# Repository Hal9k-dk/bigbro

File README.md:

# BigBro

BigBro is the system used by Hal9K to control access to its different advanced
machines, with RFID based access control.

The system is designed to cut power to the machines if no valid key-card is present
or in the special case of a 3D printer, if no special key-card is present, 
and a print isn't ongoing.

The first version of BigBro was designed around the ESP8266, specifically the WEMOS D1 mini.
Version 2 uses ESP32 with the [EspressIf ESP-IDF](https://idf.espressif.com/).

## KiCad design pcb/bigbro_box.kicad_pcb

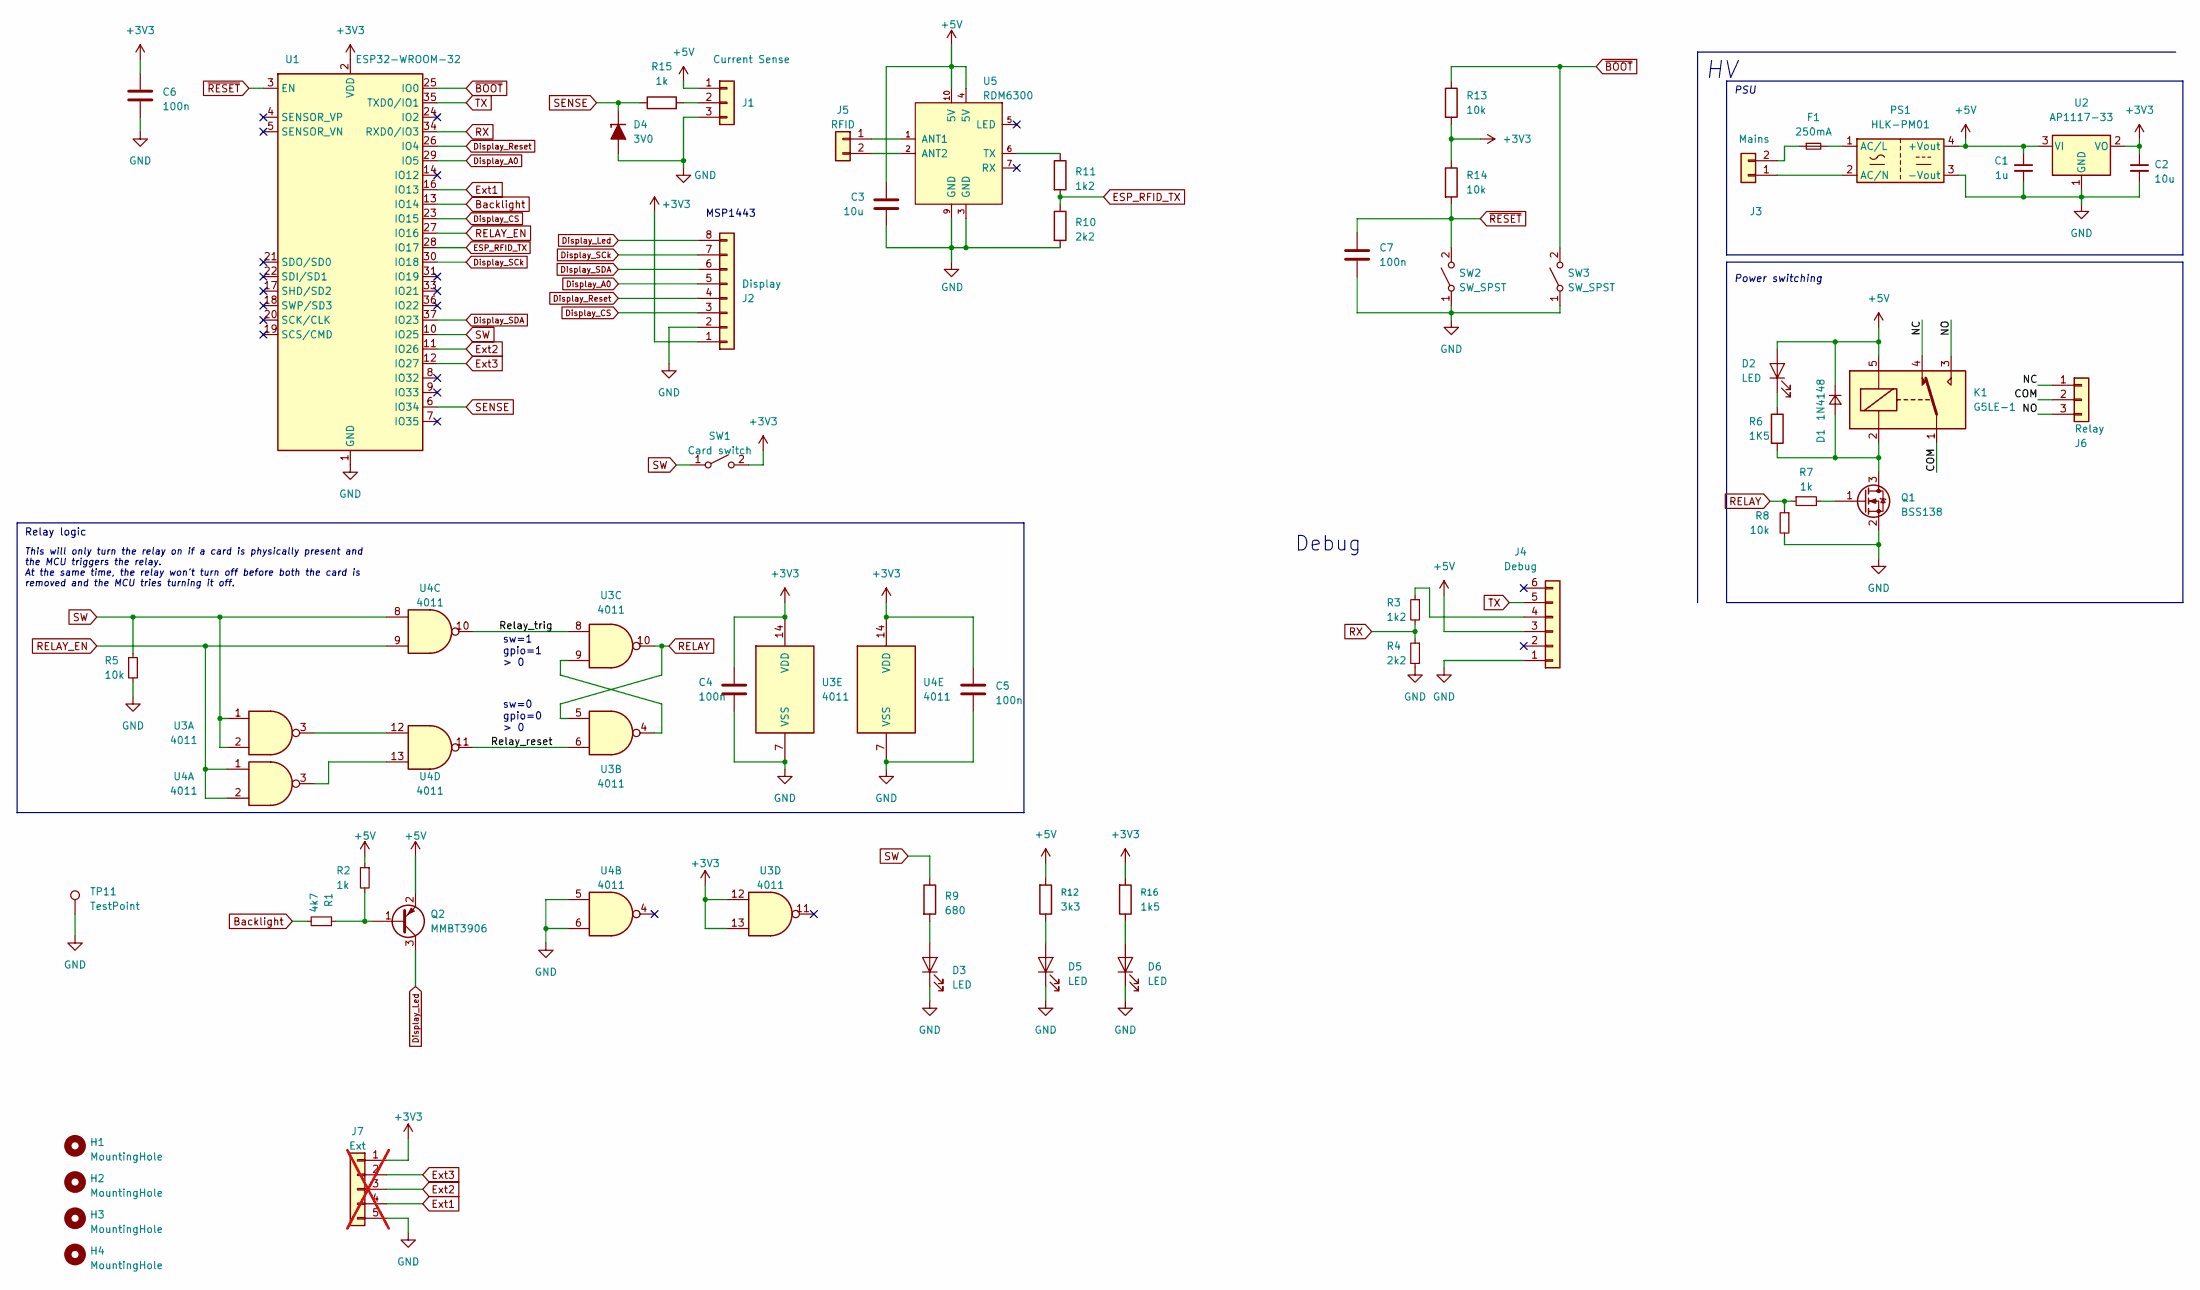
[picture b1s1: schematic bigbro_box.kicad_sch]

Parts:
C1: 1u; C_0603_1608Metric; LCSC C15849
C2: 10u; C_0603_1608Metric; LCSC C96446
C3: 10u; C_0603_1608Metric
C4, C5, C6: 100n; C_0603_1608Metric; LCSC C14663
C7: 100n; C_0603_1608Metric
D1: 1N4148; D_SOD-123
D2, D3, D5, D6: LED; LED_0603_1608Metric
D4: 3V0; D_MiniMELF
F1: 250mA; Fuse_Littelfuse_395Series
H1, H2, H3, H4: MountingHole; MountingHole_3.2mm_M3
J1: Current Sense; JST_XH_B3B-XH-A_1x03_P2.50mm_Vertical; LCSC C144394
J2: Display; PinSocket_1x08_P2.54mm_Vertical
J3: Mains; PhoenixContact_MSTBVA_2,5_2-G-5,08_1x02_P5.08mm_Vertical
J4: Debug; PinHeader_1x06_P2.54mm_Vertical; LCSC C37208
J5: RFID; JST_XH_B2B-XH-A_1x02_P2.50mm_Vertical
J6: Relay; PhoenixContact_MSTBVA_2,5_3-G-5,08_1x03_P5.08mm_Vertical
J7: Ext; PinHeader_1x05_P2.54mm_Vertical; not fitted
K1: G5LE-1; Relay_SPDT_Omron-G5LE-1
PS1: HLK-PM01; Converter_ACDC_HiLink_HLK-PMxx
Q1: BSS138; SOT-23
Q2: MMBT3906; SOT-23
R1: 4k7; R_0603_1608Metric; LCSC C23162
R2, R7: 1k; R_0603_1608Metric; LCSC C14676
R3: 1k2; R_0603_1608Metric; LCSC C22765
R4: 2k2; R_0603_1608Metric; LCSC C5362360
R5, R8: 10k; R_0603_1608Metric; LCSC C15401
R6: 1K5; R_0603_1608Metric; LCSC C22843
R9: 680; R_0603_1608Metric
R10: 2k2; R_0603_1608Metric
R11: 1k2; R_0603_1608Metric
R12: 3k3; R_0603_1608Metric
R13, R14: 10k; R_0603_1608Metric
R15: 1k; R_0603_1608Metric
R16: 1k5; R_0603_1608Metric
SW1: Card switch; JST_XH_B2B-XH-A_1x02_P2.50mm_Vertical
SW2, SW3: SW_SPST; SW_SPST_CK_RS282G05A3
TP11: TestPoint; TestPoint_Keystone_5000-5004_Miniature
U1: ESP32-WROOM-32; LCSC C95209
U2: AP1117-33; SOT-223-3_TabPin2
U3, U4: 4011; SOIC-14_3.9x8.7mm_P1.27mm
U5: RDM6300; RDM6300_B38.5x18.2mm

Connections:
+3V3: C2.1, C4.1, C5.1, C6.1, J2.1, J7.1, R13.2, R14.1, R16.1, SW1.2 (B), U1.2 (VDD), U2.2 (VO), U3.12, U3.13, U3.14 (VDD), U4.14 (VDD)
+5V: C1.1, C3.1, D1.1 (K), D2.2 (A), J1.1, J4.3, K1.5, PS1.4 (+Vout), Q2.2 (E), R2.1, R12.1, U2.3 (VI), U5.4 (5V), U5.10 (5V)
/COM: J6.2, K1.1
/NC: J6.1, K1.4
/NO: J6.3, K1.3
/Relay_reset: U3.6, U4.11
/Relay_trig: U3.8, U4.10
Backlight: R1.2, U1.13 (IO14)
Display_A0: J2.5, U1.29 (IO5)
Display_CS: J2.3, U1.23 (IO15)
Display_Led: J2.8, Q2.3 (C)
Display_Reset: J2.4, U1.26 (IO4)
Display_SCk: J2.7, U1.30 (IO18)
Display_SDA: J2.6, U1.37 (IO23)
ESP_RFID_TX: R10.1, R11.2, U1.28 (IO17)
Ext1: J7.4, U1.16 (IO13)
Ext2: J7.3, U1.11 (IO26)
Ext3: J7.2, U1.12 (IO27)
GND: C1.2, C2.2, C3.2, C4.2, C5.2, C6.2, C7.2, D3.1 (K), D4.2 (A), D5.1 (K), D6.1 (K), J1.3, J2.2, J4.1, J7.5, PS1.3 (-Vout), Q1.2 (S), R4.2, R5.2, R8.2, R10.2, SW2.1 (A), SW3.1 (A), TP11.1 (1_1), U1.1 (GND), U1.15 (GND), U1.38 (GND), U1.39 (GND), U2.1 (GND), U3.7 (VSS), U4.5, U4.6, U4.7 (VSS), U5.3 (GND), U5.9 (GND)
unnamed: D1.2 (A), K1.2, Q1.3 (D), R6.2
unnamed: D2.1 (K), R6.1
unnamed: D3.2 (A), R9.2
unnamed: D5.2 (A), R12.2
unnamed: D6.2 (A), R16.2
unnamed: J1.2, R15.2
unnamed: J3.1, PS1.2 (AC/N)
unnamed: F1.1, J3.2
unnamed: J4.4, R3.1
unnamed: J5.1, U5.1 (ANT1)
unnamed: J5.2, U5.2 (ANT2)
unnamed: F1.2, PS1.1 (AC/L)
unnamed: Q1.1 (G), R7.2
unnamed: Q2.1 (B), R1.1, R2.2
unnamed: U3.3, U4.12
unnamed: U3.4, U3.9
unnamed: U4.3, U4.13
unnamed: R11.1, U5.6 (TX)
RELAY: R7.1, R8.1, U3.5, U3.10
RELAY_EN: U1.27 (IO16), U4.1, U4.2, U4.9
RX: R3.2, R4.1, U1.34 (RXD0/IO3)
SENSE: D4.1 (K), R15.1, U1.6 (IO34)
SW: R5.1, R9.1, SW1.1 (A), U1.10 (IO25), U3.1, U3.2, U4.8
TX: J4.5, U1.35 (TXD0/IO1)
~BOOT: R13.1, SW3.2 (B), U1.25 (IO0)
~RESET: C7.1, R14.2, SW2.2 (B), U1.3 (EN)

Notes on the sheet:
Power switching
Relay logic
sw=1 gpio=1 > 0
This will only turn the relay on if a card is physically present and the MCU triggers the relay. At the same time, the relay won't turn off before both the card is removed and the MCU tries turning it off.
Debug
sw=0 gpio=0 > 0
MSP1443
PSU

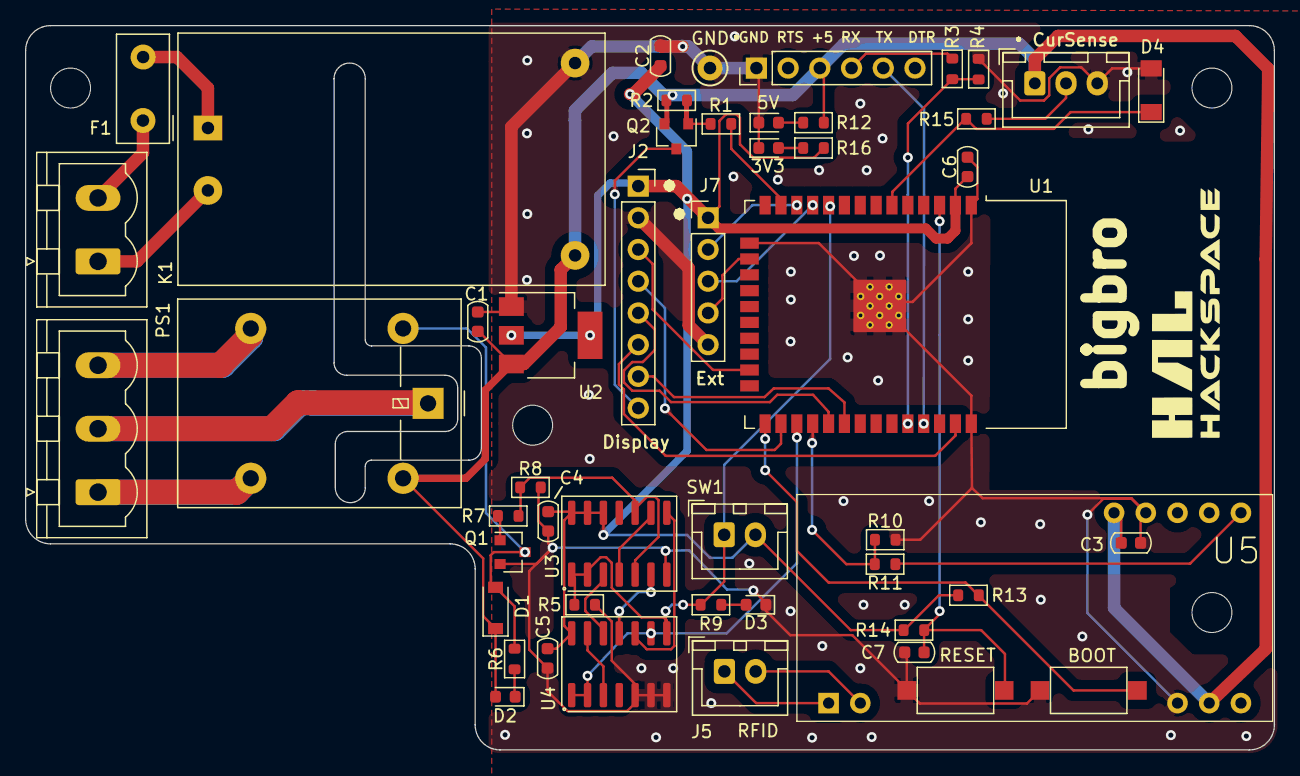
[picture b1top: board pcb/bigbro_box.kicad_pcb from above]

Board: 2 copper layers, 100.0 x 58.0 mm, 54 parts (0 on the bottom side), 45 nets.

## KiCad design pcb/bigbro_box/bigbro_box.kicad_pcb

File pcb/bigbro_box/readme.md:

# Bigbro Box

This is V2 of the access control boxes used on the machines in Hal9k.

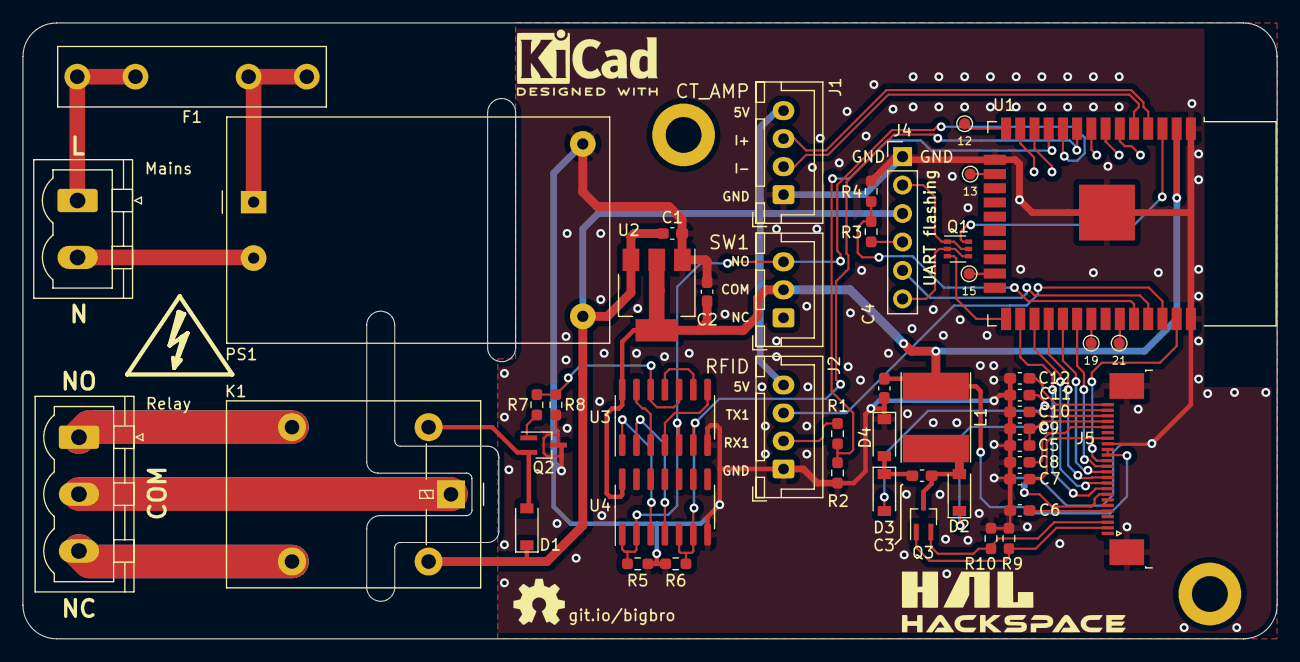
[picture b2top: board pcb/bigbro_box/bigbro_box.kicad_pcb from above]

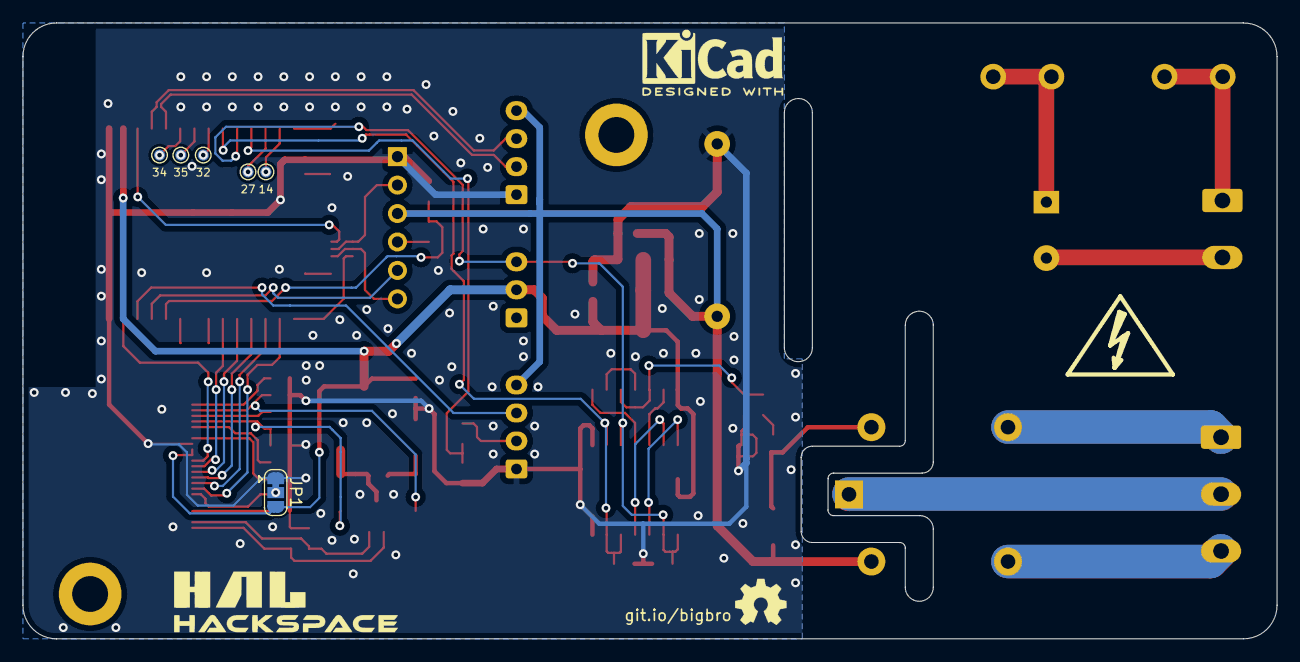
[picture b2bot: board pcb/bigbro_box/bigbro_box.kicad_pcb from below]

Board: 2 copper layers, 112.0 x 55.0 mm, 55 parts (6 on the bottom side), 59 nets.

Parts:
C1, C6, C7, C8, C9, C10, C11, C12: 1uF; C_0603_1608Metric_Pad1.08x0.95mm_HandSolder
C2: 10uF; C_0603_1608Metric_Pad1.08x0.95mm_HandSolder
C3, C4, C5: 4.7uF; C_0603_1608Metric_Pad1.08x0.95mm_HandSolder
D1: D_Small; D_SOD-123
D2, D3, D4: MBR0530; D_SOD-123
F1: 250mA; Fuseholder_Littelfuse_445_030_series_5x20mm
J1: CT_AMP; JST_XH_B4B-XH-A_1x04_P2.50mm_Vertical
J2: RFID; JST_XH_B4B-XH-A_1x04_P2.50mm_Vertical
J3: Mains; PhoenixContact_MSTBVA_2,5_2-G-5,08_1x02_P5.08mm_Vertical
J4: UART flashing; PinHeader_1x06_P2.54mm_Vertical
J5: 2-1734839-4; TE_2-1734839-4_1x24-1MP_P0.5mm_Horizontal
J6: Relay; PhoenixContact_MSTBVA_2,5_3-G-5,08_1x03_P5.08mm_Vertical
JP1: D_BS; SolderJumper-3_P1.3mm_Bridged12_RoundedPad1.0x1.5mm
K1: G5LE-1; Relay_SPDT_Omron-G5LE-1
L1: 47uH; L_Taiyo-Yuden_NR-60xx_HandSoldering
PS1: HLK-PM01; Converter_ACDC_HiLink_HLK-PMxx
Q1: ADC114YUQ; SOT-363_SC-70-6
Q2: Q_NMOS_GDS; SOT-323_SC-70_Handsoldering
Q3: Si1308EDL; SOT-323_SC-70_Handsoldering
R1, R3: 1k2; R_0603_1608Metric_Pad0.98x0.95mm_HandSolder
R2, R4: 2k2; R_0603_1608Metric_Pad0.98x0.95mm_HandSolder
R5, R6, R8: 10k; R_0603_1608Metric_Pad0.98x0.95mm_HandSolder
R7: 1k; R_0603_1608Metric_Pad0.98x0.95mm_HandSolder
R9: 1M; R_0603_1608Metric_Pad0.98x0.95mm_HandSolder
R10: 2R2; R_0603_1608Metric_Pad0.98x0.95mm_HandSolder
SW1: SW_SPDT; JST_XH_B3B-XH-A_1x03_P2.50mm_Vertical
TP1: 12; TestPoint_Pad_D1.0mm
TP2: 13; TestPoint_Pad_D1.0mm
TP3: 14; TestPoint_Pad_D1.0mm
TP4: 15; TestPoint_Pad_D1.0mm
TP5: 19; TestPoint_Pad_D1.0mm
TP6: 21; TestPoint_Pad_D1.0mm
TP7: 27; TestPoint_Pad_D1.0mm
TP8: 32; TestPoint_Pad_D1.0mm
TP9: 34; TestPoint_Pad_D1.0mm
TP10: 35; TestPoint_Pad_D1.0mm
U1: ESP32-WROOM-32
U2: AP1117-33; SOT-223-3_TabPin2
U3, U4: 4011; SOIC-14_3.9x8.7mm_P1.27mm

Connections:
+3V3: C2.1, C4.2, J5.15, J5.16, JP1.3 (B), L1.1, SW1.2 (B), U1.2 (VDD), U2.2 (VO), U3.14 (VDD), U4.14 (VDD)
+5V: C1.1, D1.1 (K), J1.4, J2.4, J4.3, K1.5, PS1.4 (+Vout), U2.3 (VI)
/COM: J6.2, K1.1
/D_BUSY: J5.9, U1.26 (IO4)
/Display/BS1: J5.8, JP1.2 (C)
/Display/GDR: J5.2, Q3.1 (G), R9.1
/Display/RESE: J5.3, Q3.2 (S), R10.1
/Display/VCOM: C12.2, J5.24
/Display/VDD: C7.2, J5.18
/Display/VGH: C5.2, C9.2, D2.1 (K), J5.21
/Display/VGL: C11.2, D3.2 (A), J5.23
/Display/VSH1: C8.2, J5.20
/Display/VSH2: C6.2, J5.5
/Display/VSL: C10.2, J5.22
/I_Sens+: J1.3, U1.4 (SENSOR_VP)
/I_Sens-: J1.2, U1.5 (SENSOR_VN)
/L_in: F1.1, J3.1
/MCU_RX0: R3.2, R4.1, U1.34 (RXD0/IO3)
/MCU_RX1: R1.2, R2.1, U1.11 (IO26)
/MCU_TX0: J4.5, U1.35 (TXD0/IO1)
/MCU_TX1: J2.3, U1.36 (IO22)
/NC: J6.3, K1.4
/NO: J6.1, K1.3
/N_in: J3.2, PS1.2 (AC/N)
/POCI: J5.14, U1.37 (IO23)
/Relay_reset: U3.3, U3.13
/Relay_trig: U3.4, U3.8
/SCK: J5.13, U1.30 (IO18)
/card_switch: R5.1, SW1.3 (C), U1.10 (IO25), U3.5, U4.1, U4.2
/relay: R7.1, R8.1, U3.10, U3.12
/relay_gpio: R6.1, U1.9 (IO33), U3.6, U4.5, U4.6
/~BOOT: Q1.3 (C1), U1.25 (IO0)
/~DTR: J4.6, Q1.2 (B2), Q1.4 (E1)
/~D_CS: J5.12, U1.29 (IO5)
/~D_D/C: J5.11, U1.28 (IO17)
/~D_RES: J5.10, U1.27 (IO16)
/~RESET: Q1.6 (C2), U1.3 (EN)
/~RTS: J4.2, Q1.1 (E2), Q1.5 (B1)
/~card_switch: U3.2, U4.4
/~relay_gpio: U3.1, U4.3
GND: C1.2, C2.2, C4.1, C5.1, C6.1, C7.1, C8.1, C9.1, C10.1, C11.1, C12.1, D4.1 (K), J1.1, J2.1, J4.1, J5.17, J5.MP (MountPin), JP1.1 (A), PS1.3 (-Vout), Q2.3 (S), R2.2, R4.2, R5.2, R6.2, R8.2, R9.2, R10.2, U1.1 (GND), U1.15 (GND), U1.38 (GND), U1.39 (GND), U2.1 (GND), U3.7 (VSS), U4.7 (VSS)
unnamed: C3.1, D2.2 (A), L1.2, Q3.3 (D)
unnamed: C3.2, D3.1 (K), D4.2 (A)
unnamed: D1.2 (A), K1.2, Q2.2 (D)
unnamed: F1.2, PS1.1 (AC/L)
unnamed: J2.2, R1.1
unnamed: J4.4, R3.1
unnamed: Q2.1 (G), R7.2
unnamed: TP1.1, U1.14 (IO12)
unnamed: TP2.1, U1.16 (IO13)
unnamed: TP3.1, U1.13 (IO14)
unnamed: TP4.1, U1.23 (IO15)
unnamed: TP5.1, U1.31 (IO19)
unnamed: TP6.1, U1.33 (IO21)
unnamed: TP7.1, U1.12 (IO27)
unnamed: TP8.1, U1.8 (IO32)
unnamed: TP9.1, U1.6 (IO34)
unnamed: TP10.1, U1.7 (IO35)
unnamed: U3.9, U3.11

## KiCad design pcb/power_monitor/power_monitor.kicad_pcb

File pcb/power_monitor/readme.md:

# Power monitoring acces system

A module based on AndersV209s work on the Wemos D1 Mini based boards.
Main changes are:

- DPST relay that breaks both Live and Neutral and handles 8A
- ACS723 10A current monitoring chip

The changes have been done to support use on 3D printers, or other machines where the user won't be expected to leave their key FOB in the device, and where the board can then determine end of use when power draw drops significantly

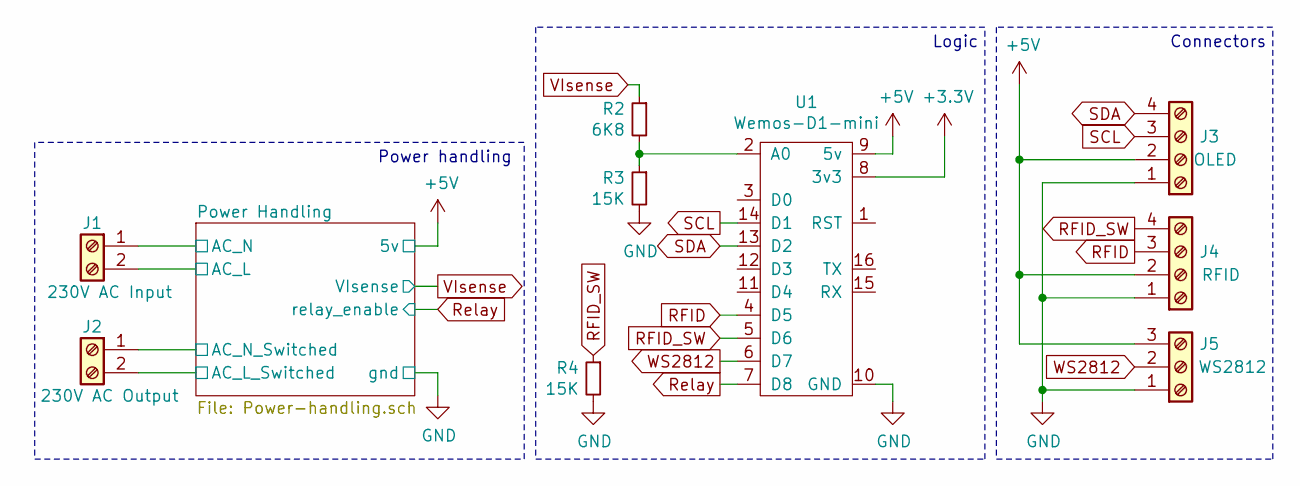
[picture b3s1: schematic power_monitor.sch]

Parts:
J1: 230V AC Input; PhoenixContact_MSTBA_2,5_2-G_1x02_P5.00mm_Horizontal
J2: 230V AC Output; PhoenixContact_MSTBA_2,5_2-G_1x02_P5.00mm_Horizontal
J3: OLED; PhoenixContact_MC_1,5_4-G-3.81_1x04_P3.81mm_Horizontal
J4: RFID; PhoenixContact_MC_1,5_4-G-3.81_1x04_P3.81mm_Horizontal
J5: WS2812; PhoenixContact_MC_1,5_3-G-3.81_1x03_P3.81mm_Horizontal
R2: 6K8; R_0603_1608Metric_Pad1.05x0.95mm_HandSolder
R3, R4: 15K; R_0603_1608Metric_Pad1.05x0.95mm_HandSolder
U1: Wemos-D1-mini; Wemos D1 Mini

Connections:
+5V: J3.2, J4.2, J5.3, U1.9 (5v); also elsewhere on the board
/Power Handling/AC_L: J1.2; also elsewhere on the board
/Power Handling/AC_L_Switched: J2.2; also elsewhere on the board
/Power Handling/AC_N: J1.1; also elsewhere on the board
/Power Handling/AC_N_Switched: J2.1; also elsewhere on the board
GND: J3.1, J4.1, J5.1, R3.2, R4.2, U1.10 (GND); also elsewhere on the board
unnamed: R2.2, R3.1, U1.2 (A0)
RFID: J4.3, U1.4 (D5)
RFID_SW: J4.4, R4.1, U1.5 (D6)
Relay: U1.7 (D8); also elsewhere on the board
SCL: J3.3, U1.14 (D1)
SDA: J3.4, U1.13 (D2)
VIsense: R2.1; also elsewhere on the board
WS2812: J5.2, U1.6 (D7)

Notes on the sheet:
Connectors
Logic
Power handling

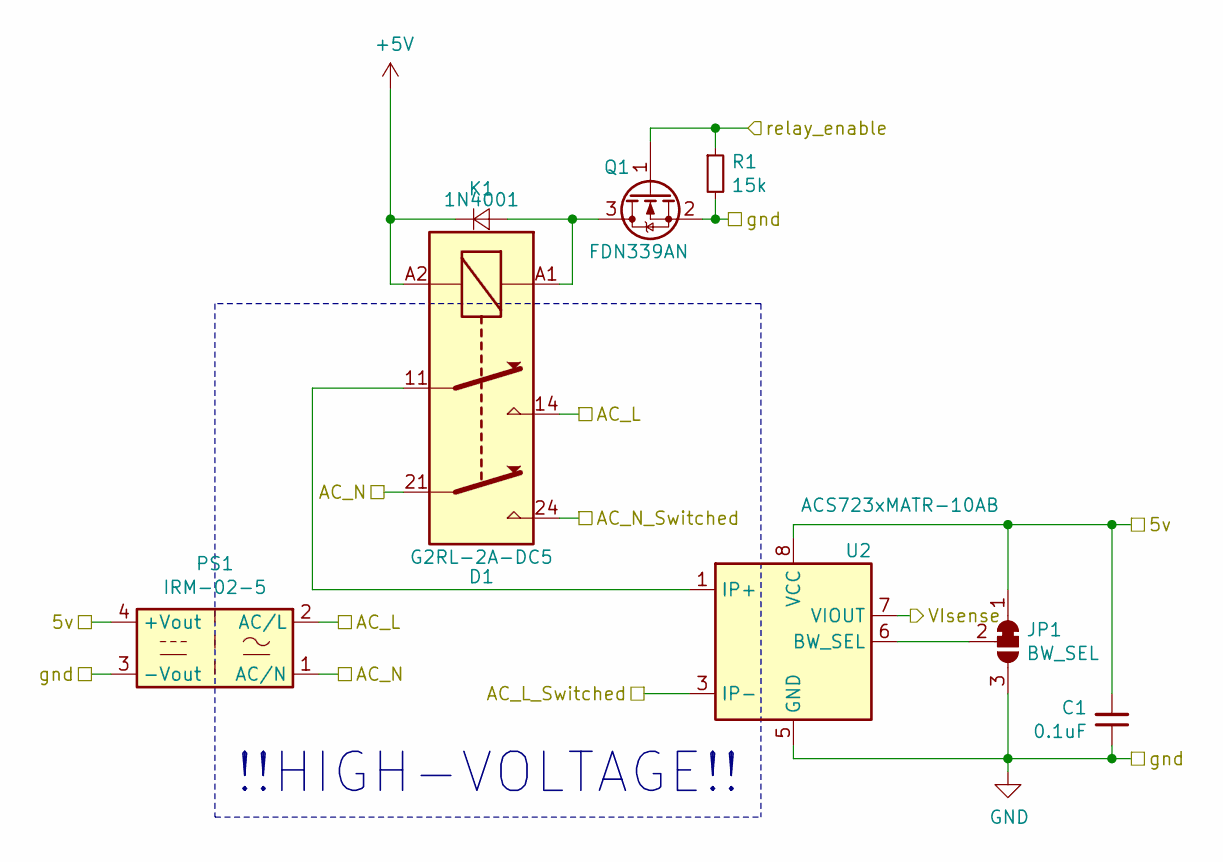
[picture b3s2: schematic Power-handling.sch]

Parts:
C1: 0.1uF; C_0603_1608Metric_Pad1.05x0.95mm_HandSolder
D1: 1N4001; D_SMA_Handsoldering
JP1: BW_SEL; SolderJumper-3_P1.3mm_Bridged2Bar12_RoundedPad1.0x1.5mm_Num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
K1: G2RL-2A-DC5; Relay_DPST_Schrack-RT2-FormA_RM5mm
PS1: IRM-02-5; Converter_ACDC_MeanWell_IRM-02-xx_THT
Q1: FDN339AN; SOT-23_Handsoldering
R1: 15k; R_0603_1608Metric_Pad1.05x0.95mm_HandSolder
U2: ACS723xMATR-10AB; SOIC-8_3.9x4.9mm_P1.27mm

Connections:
+5V: C1.2, D1.1 (K), JP1.1 (A), K1.A2, PS1.4 (+Vout), U2.8 (VCC); also elsewhere on the board
/Power Handling/AC_L: K1.14, PS1.2 (AC/L); also elsewhere on the board
/Power Handling/AC_L_Switched: U2.3 (IP-), U2.4 (IP-); also elsewhere on the board
/Power Handling/AC_N: K1.21, PS1.1 (AC/N); also elsewhere on the board
/Power Handling/AC_N_Switched: K1.24; also elsewhere on the board
GND: C1.1, JP1.3 (B), PS1.3 (-Vout), Q1.2 (S), R1.2, U2.5 (GND); also elsewhere on the board
unnamed: D1.2 (A), K1.A1, Q1.3 (D)
unnamed: JP1.2 (C), U2.6 (BW_SEL)
unnamed: K1.11, U2.1 (IP+), U2.2 (IP+)
Relay: Q1.1 (G), R1.1; also elsewhere on the board
VIsense: U2.7 (VIOUT); also elsewhere on the board

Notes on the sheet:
!!HIGH-VOLTAGE!!

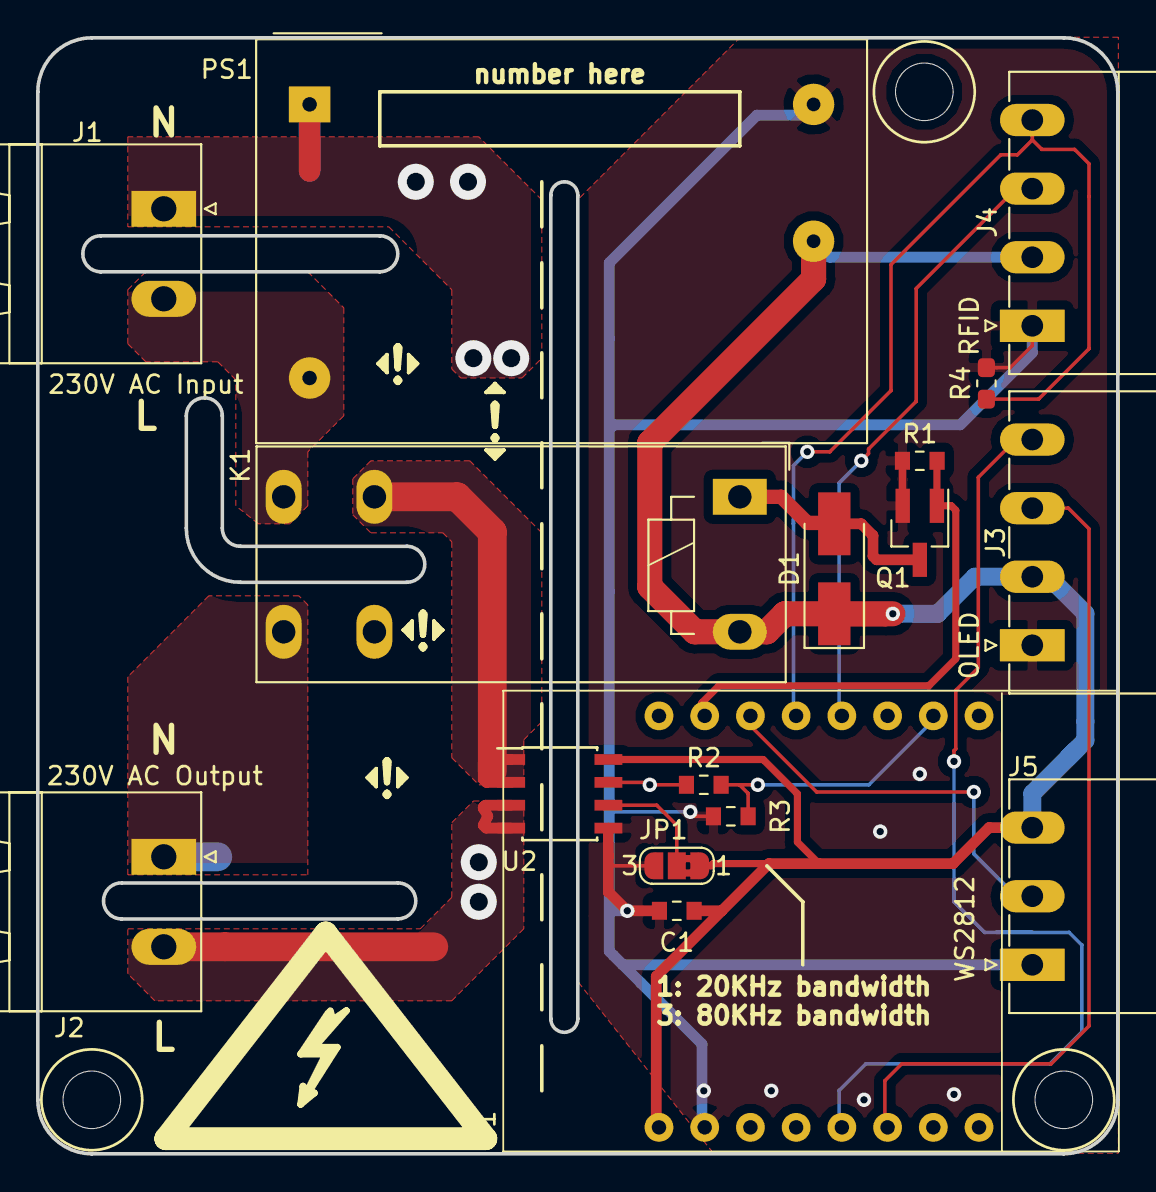
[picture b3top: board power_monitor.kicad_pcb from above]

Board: 2 copper layers, 60.0 x 62.0 mm, 17 parts (0 on the bottom side), 17 nets.

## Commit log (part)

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2018-09-15 firmware is currently weirdly broken
2018-09-15 First encounter of issues
2018-09-15 Further reduced complexity to get no interrupts
2018-09-16 further reduced test
2018-09-22 Changed tx pin to unused, as it is
2018-09-22 fixed current init
2018-09-22 More friendly screen
2018-09-23 Only check cards, not empty, for permission
2018-09-25 Streamlined wifi serial UI
2018-09-25 moved includes to header, added testing IP flag
2018-09-25 Moved to average of p2p current reading
2018-09-25 Added aditional input checks to wifi deltion
2018-09-25 minor changes
2018-09-25 Changed version to version 0.2.0
2018-09-27 enable travis ci
2018-09-27 Added newline after badge
2018-09-27 changed .travis.yml
2018-09-29 Began adding documentation
    Added doxygen config file.
    Documented main.cpp and base.h.
2018-09-29 Removed old .travis.yml
2018-09-29 Fixed Travis CI badge
    Capitalized read me file name.
2018-09-30 Added a bit of delay to show error messages on display
2018-09-30 Enabled more compiler warnings
2018-09-30 Moved flag test into header
2018-09-30 Removed averaging of current, reduced threshhold to 50mA
2018-09-30 Fixed lib_deps error
2018-10-18 Added threshhold for Ultimaker and TAZ
2018-10-18 Shit is broke
2018-10-18 made a temporary always on hack untill we can fix the stuff
2018-10-19 Revert "Shit is broke"
    This reverts commit e61f9288106303296d63b82bd6558d5188ae119d.
2018-10-19 Revert "Added threshhold for Ultimaker and TAZ"
    This reverts commit 2d10c56e86b93f1f911e7a29bbcce90c5f9df7a9.
2018-10-19 Made status line selection 0 indexed
2018-10-19 Cleaned up display, fixed inrush-current state change
2018-10-19 Incremented version, added options to dissable/enable ota
2018-10-19 Changed password for ota
2018-10-19 Increased cooldown to 9 minutes. Dissabled OTA during prints and cooldown
2018-10-19 something
2018-10-25 Fix UTF-8 display.
2018-10-31 Merged Access-System repo, into bigbro
2018-10-31 Fixed power-monitor PCB, to match real-life fixes
2018-12-10 made a state_change function to change state
2018-12-10 stored current_user_id
2018-12-10 Removed unused functions
2019-03-07 Worked on issue 8, pinned ArduinoJson to v5
2019-03-07 changed submodule to fork
2019-03-07 Implemented issue 8 fix
2019-03-07 Change to new submodule
2019-03-08 Made some values more human readable
2019-03-08 Merged changes from issue8 branch
2019-03-09 added threshhold configuration to platformio.ini
2019-03-09 Added "last user" field to eeprom
2019-03-09 made name_trunc a protected global. Cleaned up includes
2019-03-09 cleaned up includes
2019-03-09 made a "state_change" function to handle state changes
2019-03-09 Fixed potential EEPROM overflow issue
2019-03-09 Updated power_monitor pcb to use IRM-02 PSU
2019-03-09 Added folder for other PCB design
2019-03-09 Eagle files uploaded
2019-03-10 Pinned all libraries to major revision
2019-03-11 Removed submodule
2019-03-11 Moved to using PIO library for restclient
2019-03-13 Fixed library name
2019-03-13 Added build-flag to disable OTA, set SERIAL_DBG to 0 as default
2019-03-13 Trying to run CI on all controller types
2019-03-13 Set run to verbose for this test
2019-03-13 Added pragmas
2019-03-13 Added more pragma
2019-03-13 Disabled verbose output
2019-03-13 Only build platformio, and cancel builds if only docs changed
2019-03-13 Changed doc file to check new travis script
2019-03-13 Fixed spelling mistake
2019-03-15 added "clear" function Sets buffer to threshhold. So any new readings either screw the average up or down.
2019-03-15 Changed threshhold fr the UM
2019-03-15 Fixed printer thinking it was printing for the first minute
2019-03-15 Added super verbose serial dbg
2019-03-15 Set ota pwd to default. OTA will be disabled in production units
2019-03-15 Fixed inrush prevention function
2019-03-15 Finished up new printer code
2019-03-19 Documented Printer and ACS class
2019-03-19 Set up automated doxygen build and deployment to gh-pages
2019-03-19 Moved to much cleaner documentation generation
2019-03-19 fixed deployment branch
2019-03-19 Implemented main page for doxygen
2019-03-19 Updated main page formatting
2019-03-19 Fixed some variable descriptions
2019-03-19 More documentation
2019-03-20 Moved to single 'set_lines' function in display class
2019-09-05 A lot of stuff I can't remember, and fastled rate limit
2019-10-25 Cleanup.
2019-10-25 Bump REST client version.
2019-10-28 Add debug functions, fix peak-to-peak calculation.
2019-10-28 Add debug.
2019-10-28 Revert debug.
2019-11-28 Clear status when card is removed.
2019-11-28 while -> if
2020-01-30 Reduce debug noise.
2020-02-06 Untabify.
2020-02-06 Add lots of info in the display, make a bunch of gratuitous changes.
2020-02-06 Fix conflicts.
2020-02-06 Deploy Hal9k-dk/bigbro to github.com/Hal9k-dk/bigbro.git:gh-pages
2021-10-11 Added v2 schematic
2021-10-11 Added resistive divider to RX0
2021-10-17 Moved to SPDT relay, added 24pin FPC for e-ink
2021-10-17 Widened isolation slot
2021-10-21 Order1
2022-09-01 Add files via upload
    var begyndt på skift til andet display 1,44"
    https://www.aliexpress.com/item/4000219159401.html?spm=a2g0o.order_list.0.0.4b8d1802SihISr
2023-03-23 Add from zip file.
2023-03-30 Remove unneeded pulldown.
2023-04-01 Add local libs/footprints. Add GND testpoint.
2023-04-01 Update README for V2.
2023-04-01 Change to RDM6300, etc.
2023-04-02 New fuse holder, rearrange footprints.
2023-04-02 Optimize allocation of gates.
2023-04-02 Change current sense to single pin.
2023-04-03 Add 3D model for RDM6300 socket.
2023-04-03 Add 3D model for fuse holder.
2023-04-03 Route flip-flop, reduce width to 100 mm.
2023-04-03 Finish routing.
2023-04-03 Add extension connector.
2023-04-03 Fill zones.
2023-04-04 Remove solder mask on high-current traces.
2023-04-04 Add 3D model.
2023-04-04 Clarify connector labels.
2023-04-04 Order.
2023-05-06 Improve debug connector labels.
2023-05-06 Move display backlight from GPIO12 to GPIO14 to fix boot problem.
2023-05-06 Add reset and boot switches.
2023-05-06 Add ESP32 skeleton code.
2023-05-06 Add console interface.
2023-05-06 Add voltage divider for RFID.
2023-05-06 Increase value of switch LED resistor.
2023-05-06 Add command to read switch; initialize switch GPIO.
2023-05-13 Add simple HW test program.
2023-05-13 Add symbolic names.
2023-05-13 Use RDM6300 protocol.
2023-05-13 Make rfid command work.
2023-05-13 Add RFID pin.
2023-05-13 Add delay.
2023-05-13 Enable display CS.
2023-05-13 Flip display connector.
2023-05-14 Swap S and D on Q3.
2023-05-14 Forgot to save
2023-05-15 Connect to WiFi.
2023-05-18 Make WiFi code work.
2023-06-01 PoC for coil holder.
2023-06-01 PoC for switch holder.
2023-06-02 Adjust to fit.
2023-06-03 Adjust.
2023-06-15 Fix Q3 footprint, Q4 resistor values.
2023-06-15 Use PWM for display backlight.
2023-06-17 Tweak.
2023-06-17 Control backlight manually.
2023-06-28 Add case front.
2023-07-02 Achieve perfection.
2023-07-02 First attempt of front.
2023-07-03 Enlarge card pocket slightly.
2023-07-03 First attempt.
2023-07-03 Fix bugs.
2023-07-04 Increase width of switch opening.
2023-07-04 Basic bottom.
2023-07-04 Add PCB standoffs.
2024-02-04 Tweak; add wall fittings.
2024-02-04 Update ESP-IDF.
2024-02-04 Move.
2024-02-04 Remove old OpenSCAD files.
2024-02-05 Remove unused function.
2024-02-05 Tweak insert hole.
2024-02-09 Fix display clip position.
2024-02-09 Make display retainers a bit smaller.
2024-02-14 Copy lots of stuff from ACS frontend.
2024-02-14 Add more test commands.
2024-02-16 Add GW credentials.
2024-02-17 Implement controller FSA.
2024-02-17 Start implementing display class.
2024-02-19 Switch to new display driver.
2024-02-20 More work on display class.
2024-02-24 Finish basic display functionality.
2024-02-25 Fix bug where first progress line was lost.
2024-02-25 Turn backlight on.
2024-02-25 Fix backlight config.
2024-02-25 Implement time display.
2024-03-15 Fix time display.
2024-03-16 Work on controller logic.
2024-03-16 Fix display bugs.
2024-03-16 Always trust the cache.
2024-03-16 Show user name.
2024-03-16 Use small font for user name.
2024-03-24 Add RTS pullup.
2024-08-04 Add OTA FWU support.
2024-08-04 Cosmetic updates.
2024-09-06 Thicker.
2024-09-06 Fix too little room for switch.
2024-09-07 Add support for horizontal orientation.
2024-09-07 Reduce insert size slightly.
2024-09-15 Add PDF
2024-09-15 Add schematic.
2024-10-05 Fix bug where screw holes are offset.
2024-10-05 Special version.
2024-10-11 Reduce insert radius.
2024-10-18 Strain relief for cable.
2024-10-31 Add C6.
2024-11-04 Show identifier on boot.
2024-11-04 Do OTA check before starting threads.
2024-11-04 Fix ident display.
2024-11-07 Reduce log noise.
2024-11-07 Extend logger test.
2024-11-07 Clean up logging.
2024-11-28 Change C3 to 0608.
2024-12-25 Add WiFi indicator.
2024-12-28 Do not show 'Unknown' with no card ID.
2024-12-29 Use v3 of the API to allow handling 'no access' scenario.
2024-12-29 Initialize ADC channel, adjust messages.
2024-12-29 Add thermal pad.
2024-12-29 Updates.
2024-12-30 KiCad 9.
2024-12-30 Use a smaller fuse.
2024-12-31 Make countersink deeper.
2025-02-22 Add extra transistor.
2025-02-22 Route.
2025-02-24 Start adding JLCPCB part numbers.
2025-02-27 Add stencil.
2025-03-04 Improve debug, remove unused struct member, fix deprecations.
2025-03-13 Implement scheduled reboot.
2025-03-20 Update stencil.
2025-03-20 Enlarge ESP32 pads.
2025-03-21 Use another filename for firmware for V2 HW.
2025-04-20 Update display config, etc.
2025-04-20 Remove solder mask from relay traces.
2025-04-21 Force update if BOOT is pressed.
2025-04-21 Add resistor divider for current sense input.
2025-04-21 Start adding support for current sensor.
2025-05-01 Use zener.
2025-06-04 Add current sense task.
2025-06-04 Fix display issues.
2025-06-04 Use interrupt for current sensor.
2025-06-05 Remove return code check for esp_event_handler_unregister().
2025-07-13 Refactor.
2025-07-13 Implement current sense mode.
2025-07-14 Holder for WCS1x00 current sensor module.
2025-07-14 Bottom with cutouts for plugs.
2025-07-15 Add cutouts for retaining clips.
2025-07-29 Rename.
2025-08-01 Add holes on left side.
2025-08-02 Reduce insert hole size.
2025-10-17 ESP-IDF 5.5.1.
2025-11-20 Require three keypresses to enter debug mode.
2026-05-28 Update for ESP-IDF 6. Add MQTT support.
2026-05-28 Bump.
2026-05-30 Fix debug mode check.
2026-05-30 Disable cert check.
2026-05-30 Fix debug mode check, for real. Disable OTA check if EXT1 is pulled low.
2026-05-30 Add pin defs.
2026-05-30 Remove unneeded transistors and resistors.
2026-06-05 Revert "Disable cert check."
    This reverts commit b48e8d643a94ec2915a7033f8de10bf629965834.
2026-06-13 Enable pullup on EXT pins.
2026-06-13 Convert to MQTT.
2026-06-13 Reduce code size.
2026-06-13 Disable OTA FWU if card switch is active.
2026-06-13 Sync with v2.
2026-06-19 Simplify debug circuitry.
2026-06-19 Add power LEDs.
2026-06-28 Update scripts
2026-06-28 Align version number with HW revision.
2026-06-30 Include card_present in MQTT status.
